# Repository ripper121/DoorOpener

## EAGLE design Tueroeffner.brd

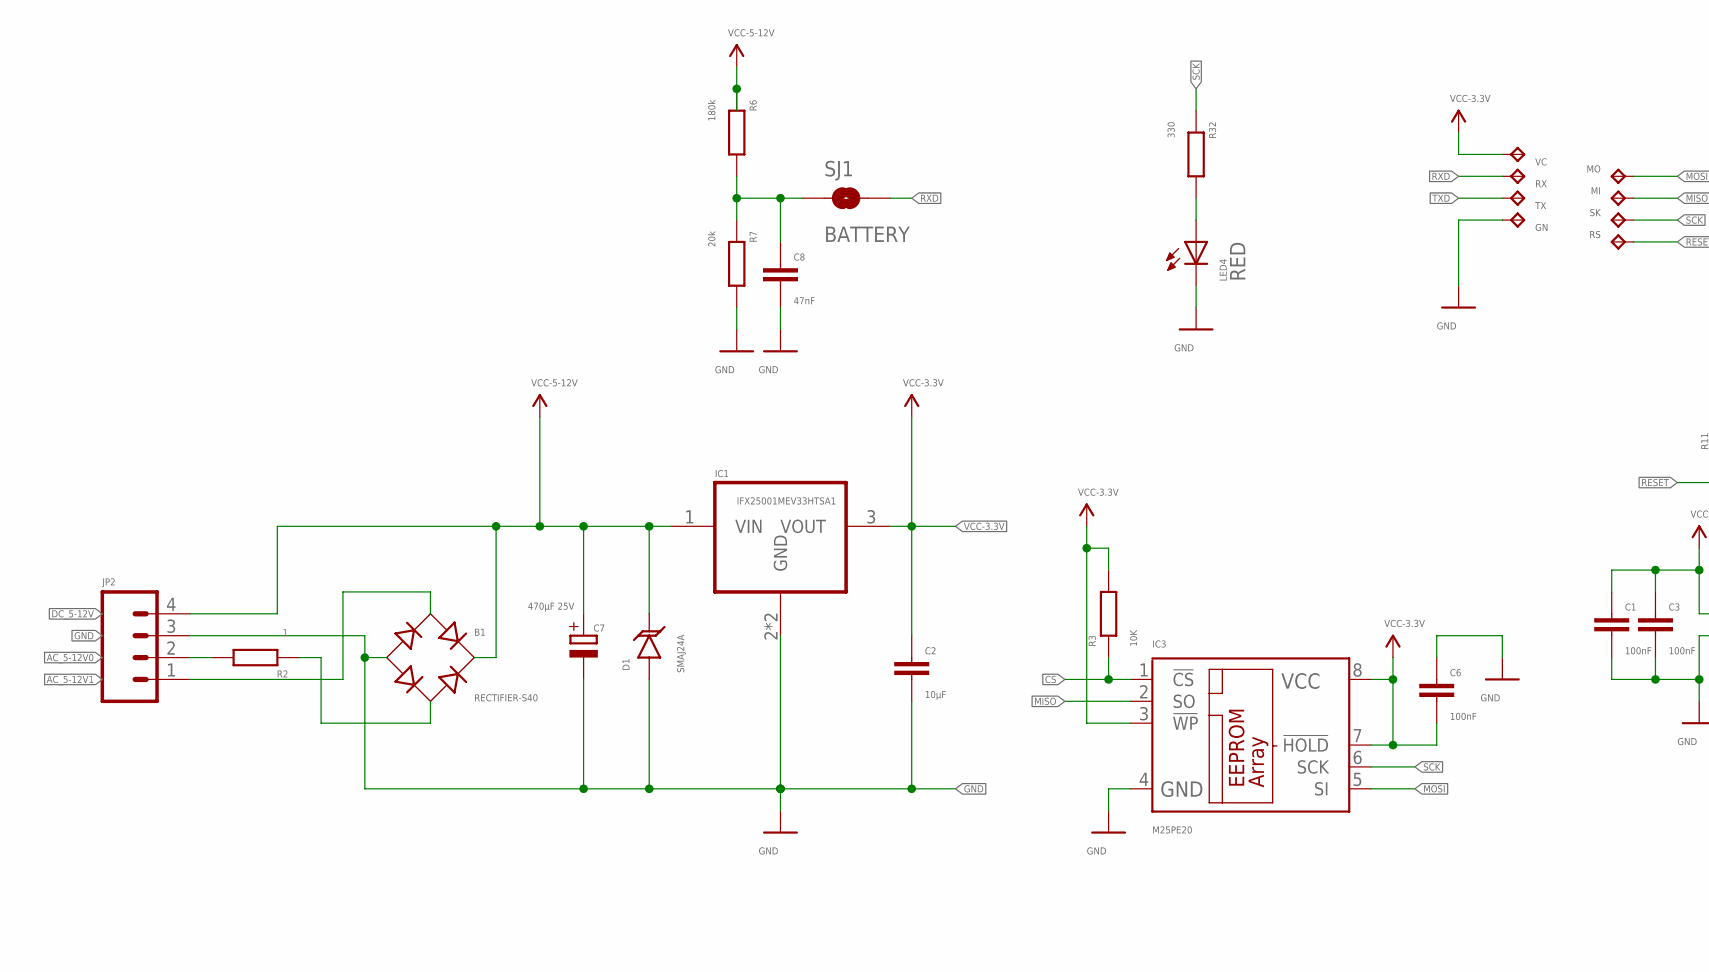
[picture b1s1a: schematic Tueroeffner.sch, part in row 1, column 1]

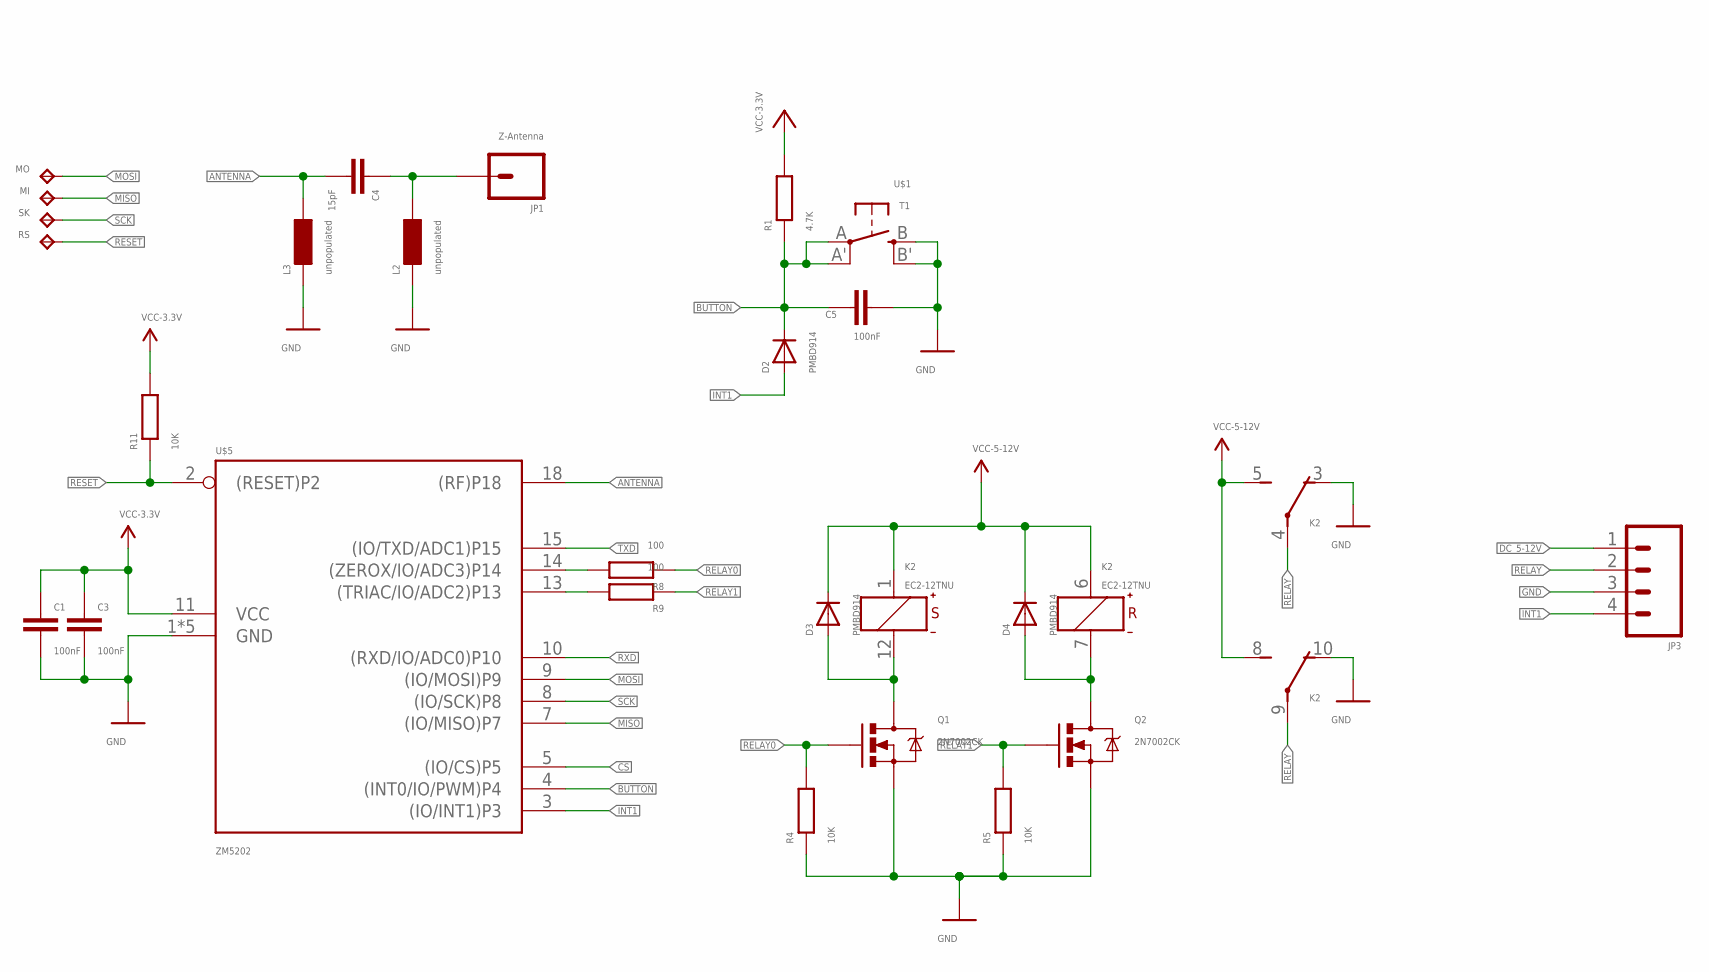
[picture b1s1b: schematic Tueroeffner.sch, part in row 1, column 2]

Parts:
B1: RECTIFIER-S40; TO-269AA
C1, C3, C6: 100nF; C2012
C2: 10µF; C0805
C4: 15pF; C2012
C5: 100nF; C0805
C7: 470µF 25V; 175TMP-0810
C8: 47nF; C2012
D1: SMAJ24A; SMA-DIODE
D2, D3, D4: PMBD914; SOT23
GN: TPTP14R; TP14R
IC1: IFX25001MEV33HTSA1; SOT223
IC3: M25PE20; SO-08
JP1: Z-Antenna; 1X01
JP2, JP3: M04SCREW; SCREWTERMINAL-3.5MM-4
K2: EC2-12TNU; TX2-L2
L2, L3: unpopulated; L2012C
LED4: RED; CHIP-LED0805
MI: TPTP14R; TP14R
MO: TPTP14R; TP14R
Q1, Q2: 2N7002CK; SOT23-3
R1: 4.7K; M0805
R2: 1; M2012
R3, R4, R5, R11: 10K; M2012
R6: 180k; M2012
R7: 20k; M2012
R8, R9: 100; M2012
R32: 330; M2012
RS: TPTP14R; TP14R
RX: TPTP14R; TP14R
SJ1: BATTERY; SJ_2S-TRACE
SK: TPTP14R; TP14R
TX: TPTP14R; TP14R
U$1: T1; EVQ-Q2
U$5: ZM5202; ZM5202_STERN
VC: TPTP14R; TP14R

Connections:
AC_5-12V0: JP2.2, R2.2
AC_5-12V1: B1.AC1, JP2.1
ANTENNA: C4.2, L3.1, U$5.18 ((RF)P18)
BUTTON: C5.1, D2.3 (C), R1.1, U$1.A, U$1.A' (P1), U$5.4 ((INT0/IO/PWM)P4)
CS: IC3.1 (!CS), R3.1, U$5.5 ((IO/CS)P5)
DC_5-12V: B1.+, C7.+, D1.C, D3.3 (C), D4.3 (C), IC1.1 (VIN), JP2.4, JP3.1, K2.1 (+), K2.5 (S), K2.6 (+), K2.8 (S), R6.1
GND: B1.-, C1.2, C2.2, C3.2, C5.2, C6.1, C7.-, C8.2, D1.A, GN.TP, IC1.2 (GND), IC1.4 (GND), IC3.4 (GND), JP2.3, JP3.3, K2.3 (O), K2.10 (O), L2.2, L3.2, LED4.C, Q1.2 (S), Q2.2 (S), R4.1, R5.1, R7.2, U$1.B (S), U$1.B' (S1), U$5.1 (GND), U$5.6 (GND), U$5.12 (GND), U$5.16 (GND), U$5.17 (GND)
INT1: D2.1 (A), JP3.4, U$5.3 ((IO/INT1)P3)
MISO: IC3.2 (SO), MI.TP, U$5.7 ((IO/MISO)P7)
MOSI: IC3.5 (SI), MO.TP, U$5.9 ((IO/MOSI)P9)
unnamed: B1.AC2, R2.1
unnamed: C8.1, R6.2, R7.1, SJ1.1
unnamed: R8.2, U$5.14 ((ZEROX/IO/ADC3)P14)
unnamed: R9.2, U$5.13 ((TRIAC/IO/ADC2)P13)
unnamed: D3.1 (A), K2.12 (-), Q1.3 (D)
unnamed: D4.1 (A), K2.7 (-), Q2.3 (D)
unnamed: LED4.A, R32.2
unnamed: C4.1, JP1.1, L2.1
RELAY: JP3.2, K2.4, K2.9
RELAY0: Q1.1 (G), R4.2, R8.1
RELAY1: Q2.1 (G), R5.2, R9.1
RESET: R11.1, RS.TP, U$5.2 ((RESET)P2)
RXD: RX.TP, SJ1.2, U$5.10 ((RXD/IO/ADC0)P10)
SCK: IC3.6 (SCK), R32.1, SK.TP, U$5.8 ((IO/SCK)P8)
TXD: TX.TP, U$5.15 ((IO/TXD/ADC1)P15)
VCC-3.3V: C1.1, C2.1, C3.1, C6.2, IC1.3 (VOUT), IC3.3 (!WP), IC3.7 (!HOLD), IC3.8 (VCC), R1.2, R3.2, R11.2, U$5.11 (VCC), VC.TP

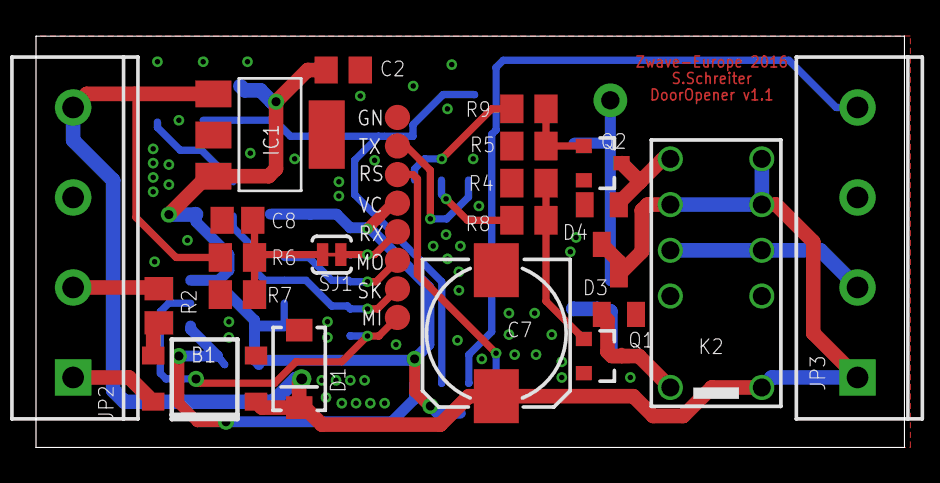
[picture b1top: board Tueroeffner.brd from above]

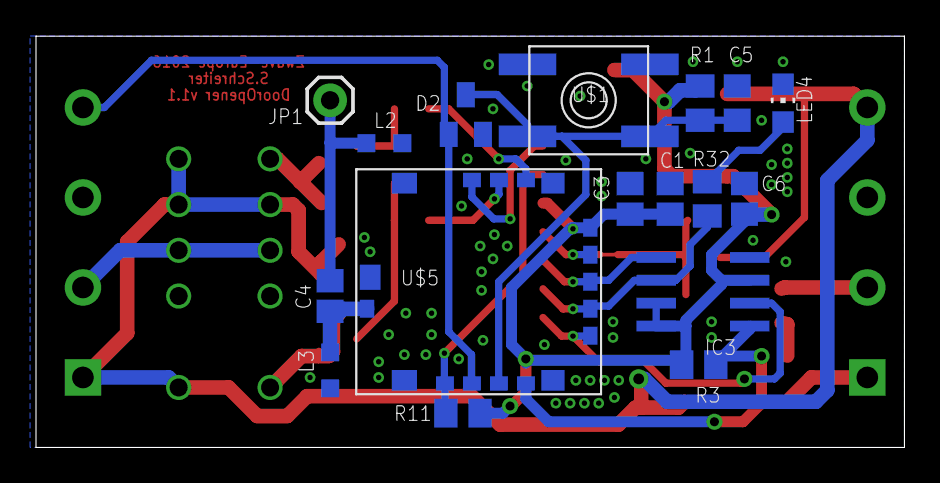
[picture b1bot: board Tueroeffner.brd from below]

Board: 2 copper layers, 48.2 x 22.9 mm, 46 parts (17 on the bottom side), 26 nets.

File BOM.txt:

Stückliste exportiert aus C:/Users/sts/Documents/eagle/DoorOpener/Tueroeffner.sch am 15.01.2016 14:01

Qty Value             Device                Package               Parts                          Description                                           MF                 MPN                OC_FARNELL OC_NEWARK PROD_ID     SPICEMODEL SPICEPREFIX TP_SIGNAL_NAME VALUE    
2                     M04SCREW              SCREWTERMINAL-3.5MM-4 JP2, JP3                       Header 4                                                                                                                                                                    
1   1                 R-EU_M2012            M2012                 R2                             RESISTOR, European symbol                                                                                                                                                   
2   100               R-EU_M2012            M2012                 R8, R9                         RESISTOR, European symbol                                                                                                                                                   
1   100nF             C-EUC0805             C0805                 C5                             CAPACITOR, European symbol                                                                                                                                                  
3   100nF             CC2012                C2012                 C1, C3, C6                     CAPACITOR, European symbol                                                                                                   NONE       C                                   
4   10K               R-EU_M2012            M2012                 R3, R4, R5, R11                RESISTOR, European symbol                                                                                                                                                   
1   10µF              C-EUC0805             C0805                 C2                             CAPACITOR, European symbol                                                                                                                                                  
1   15pF              CC2012                C2012                 C4                             CAPACITOR, European symbol                                                                                                   NONE       C                                   
1   180k              R-EU_M2012            M2012                 R6                             RESISTOR, European symbol                                                                                                                                                   
1   20k               R-EU_M2012            M2012                 R7                             RESISTOR, European symbol                                                                                                                                                   
2   2N7002CK          MOSFET-NCHANNELBSS138 SOT23-3               Q1, Q2                         Common NMOSFET Parts                                                                                             TRANS-00830                                       200mA/50V
1   330               R-EU_M2012            M2012                 R32                            RESISTOR, European symbol                                                                                                                                                   
1   4.7K              R-EU_M0805            M0805                 R1                             RESISTOR, European symbol                                                                                                                                                   
1   470µF 25V         CPOL-EU175TMP-0810    175TMP-0810           C7                             POLARIZED CAPACITOR, European symbol                                                                                                                                        
1   EC2-12TNU         TX2-L2-12V            TX2-L2                K2                             TX Relay 2 coil latching NAiS                         AROMAT/ MATSUSHITA TX2-L2-12V         1124060    64K3213                                                              
1   M25PE20           25LC080SN             SO-08                 IC3                            Serial EEPROM 4K/ 8K , SPI bus                                           25LC320A                                                                                           
1   NCV4264-2ST33T3G  REG1118               SOT223                IC1                            800mA Low Dropout (LDO) Positive Regulator                               REG1118-2.85/2K5G4 unknown    14M2185                                                              
3   PMBD914           D-A1-C3               SOT23                 D2, D3, D4                     DIODE                                                                                                                                                                       
1   RECTIFIER-S40     RECTIFIER-S40         TO-269AA              B1                             Rectifier                                                                                                                                                                   
1   RED               LEDCHIP-LED0805       CHIP-LED0805          LED4                           LED                                                                                                                                                                         
1   SMAJ20A           TVSSMA                SMA-DIODE             D1                             Transient voltage suppressor- prevents ESD on inputs.                                                                                                                       
1   SOLDERJUMPERTRACE SOLDERJUMPERTRACE     SJ_2S-TRACE           SJ1                            Solder Jumper                                                                                                                                                               
1   T1                EVQQ2                 EVQ-Q2                U$1                            SMT 6mm switch, EVQQ2 series                                                                                                                                                
8   TPTP14R           TPTP14R               TP14R                 GN, MI, MO, RS, RX, SK, TX, VC Test pad                                                                                                                                                                    
1   Z-Antenna         M01PTH                1X01                  JP1                            Header 1                                                                                                                                                                    
1   ZM5202            ZM5202ZM5202_STERN    ZM5202_STERN          U$5                            ZM5202                                                                                                                                                                      
2   unpopulated       LL2012C               L2012C                L2, L3                         INDUCTOR, European symbol                                                                                                    NONE       L

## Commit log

2016-01-04 First Version
    Some errors with the relay driver.
2016-01-04 New H-Bridge
2016-01-04 Basic Routing
2016-01-04 RC 2.0
2016-01-05 lck ign
2016-01-05 New Relais designe
2016-01-07 Semi Routed
2016-01-07 ign file
2016-01-07 Auto Router
2016-01-07 RC candidate
2016-01-07 Clean Up
2016-01-07 Gerber
2016-01-07 Cleanup
2016-01-08 little layout changes
2016-01-11 Final RC
2016-01-12 Add voltage divider
2016-01-18 Voltage Divider Cap
2016-01-19 Issue Text
2016-01-20 Remove Source Code
2016-01-20 Typo
2016-01-20 Button+Led to Top

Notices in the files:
parts and their libraries:
SparkFun-DiscreteSemi: Licensing: Creative Commons ShareAlike 4.0 International - https://creativecommons.org/licenses/by-sa/4.0
